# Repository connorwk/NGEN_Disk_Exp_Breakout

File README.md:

# NGEN Disk Expansion Breakout

Breakout for the NGEN Floppy disk and Hard disk controller to add a secondary external disk drive.

A photo of the expansion unit:

I reverse engineered it making a [Schematic](Schematic.pdf) which you can easily solder up on a perf board, or I laid out a simple board which you could order from a board house if you wish:

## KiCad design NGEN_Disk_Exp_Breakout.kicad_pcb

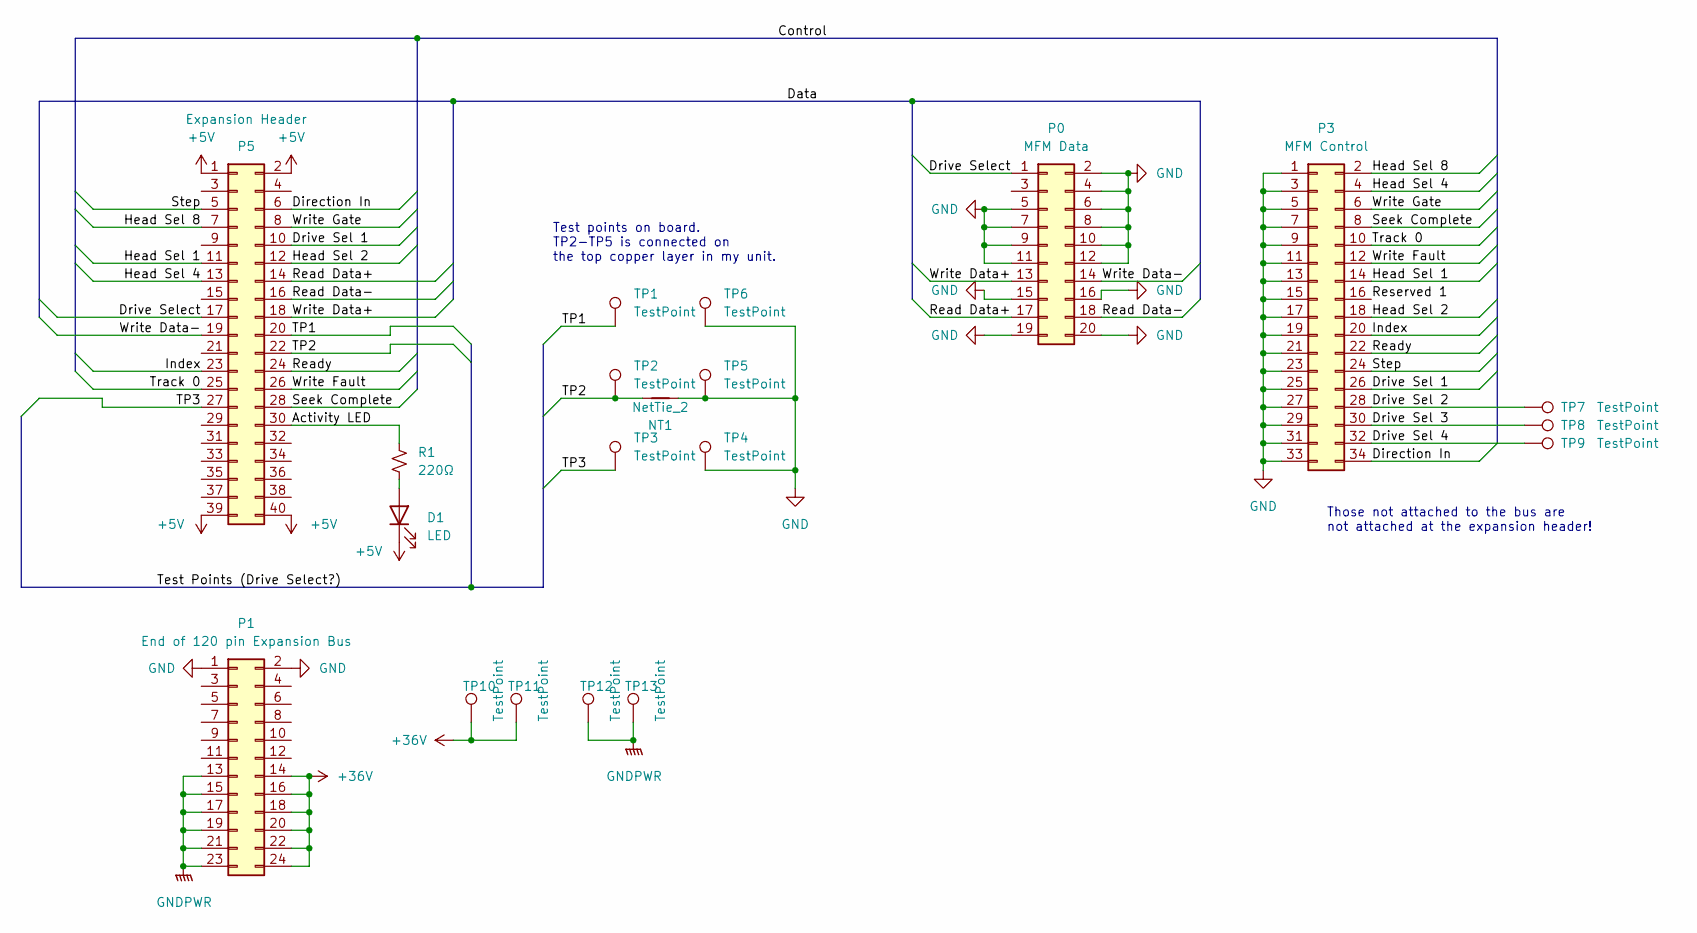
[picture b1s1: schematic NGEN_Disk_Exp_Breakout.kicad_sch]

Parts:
D1: LED; LED_D3.0mm
NT1: NetTie_2; NetTie-2_SMD_Pad0.5mm
P0: MFM Data; IDC-Header_2x10_P2.54mm_Vertical
P1: End of 120 pin Expansion Bus; PinHeader_2x12_P2.54mm_Horizontal
P3: MFM Control; IDC-Header_2x17_P2.54mm_Vertical
P5: Expansion Header; PinHeader_2x20_P2.54mm_Horizontal
R1: 220Ω; R_Axial_DIN0204_L3.6mm_D1.6mm_P7.62mm_Horizontal
TP1, TP2, TP3, TP4, TP5, TP6, TP7, TP8, TP9, TP10, TP11, TP12, TP13: TestPoint; TestPoint_Loop_D1.80mm_Drill1.0mm_Beaded

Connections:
+5V: D1.1 (K), P5.1, P5.2, P5.39, P5.40
+36V: P1.14, P1.16, P1.18, P1.20, P1.22, P1.24, TP10.1, TP11.1
/Activity LED: P5.30, R1.1
/Direction In: P3.34, P5.6
/Drive Sel 1: P3.26, P5.10
/Drive Sel 2: P3.28, TP7.1
/Drive Sel 3: P3.30, TP8.1
/Drive Sel 4: P3.32, TP9.1
/Drive Select: P0.1, P5.17
/Head Sel 1: P3.14, P5.11
/Head Sel 2: P3.18, P5.12
/Head Sel 4: P3.4, P5.13
/Head Sel 8: P3.2, P5.7
/Index: P3.20, P5.23
/Read Data+: P0.17, P5.14
/Read Data-: P0.18, P5.16
/Ready: P3.22, P5.24
/Reserved 1: P3.16
/Seek Complete: P3.8, P5.28
/Step: P3.24, P5.5
/TP1: P5.20, TP1.1
/TP2: NT1.2, P5.22, TP2.1
/TP3: P5.27, TP3.1
/Track 0: P3.10, P5.25
/Write Data+: P0.13, P5.18
/Write Data-: P0.14, P5.19
/Write Fault: P3.12, P5.26
/Write Gate: P3.6, P5.8
GND: NT1.1, P0.2, P0.4, P0.5, P0.6, P0.7, P0.8, P0.9, P0.10, P0.11, P0.12, P0.15, P0.16, P0.19, P0.20, P1.1, P1.2, P3.1, P3.3, P3.5, P3.7, P3.9, P3.11, P3.13, P3.15, P3.17, P3.19, P3.21, P3.23, P3.25, P3.27, P3.29, P3.31, P3.33, TP4.1, TP5.1, TP6.1
GNDPWR: P1.13, P1.15, P1.17, P1.19, P1.21, P1.23, TP12.1, TP13.1
unnamed: D1.2 (A), R1.2

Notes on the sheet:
Those not attached to the bus are not attached at the expansion header!
Test points on board. TP2-TP5 is connected on the top copper layer in my unit.

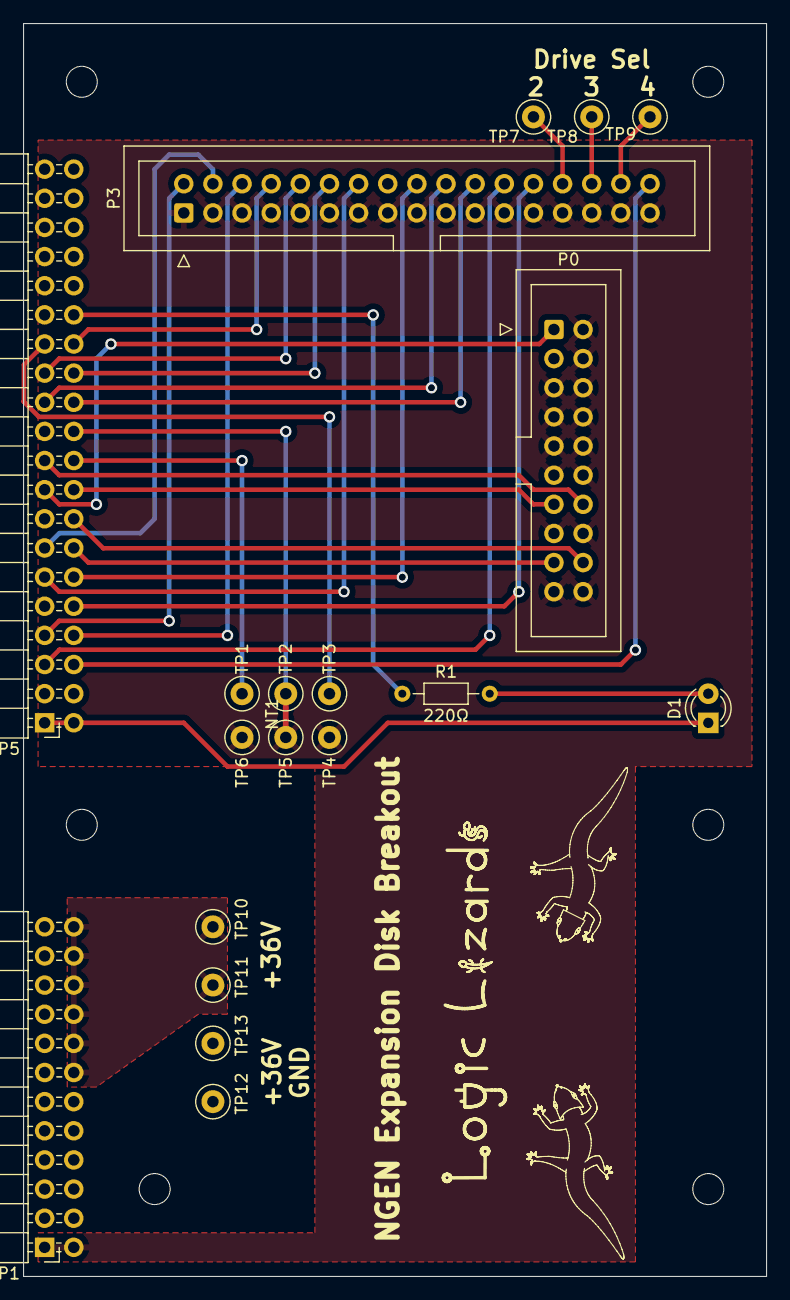
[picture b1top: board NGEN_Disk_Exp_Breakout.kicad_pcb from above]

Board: 2 copper layers, 64.8 x 109.2 mm, 20 parts (0 on the bottom side), 30 nets.

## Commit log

2022-03-17 Readme
2022-03-17 Photo and update
